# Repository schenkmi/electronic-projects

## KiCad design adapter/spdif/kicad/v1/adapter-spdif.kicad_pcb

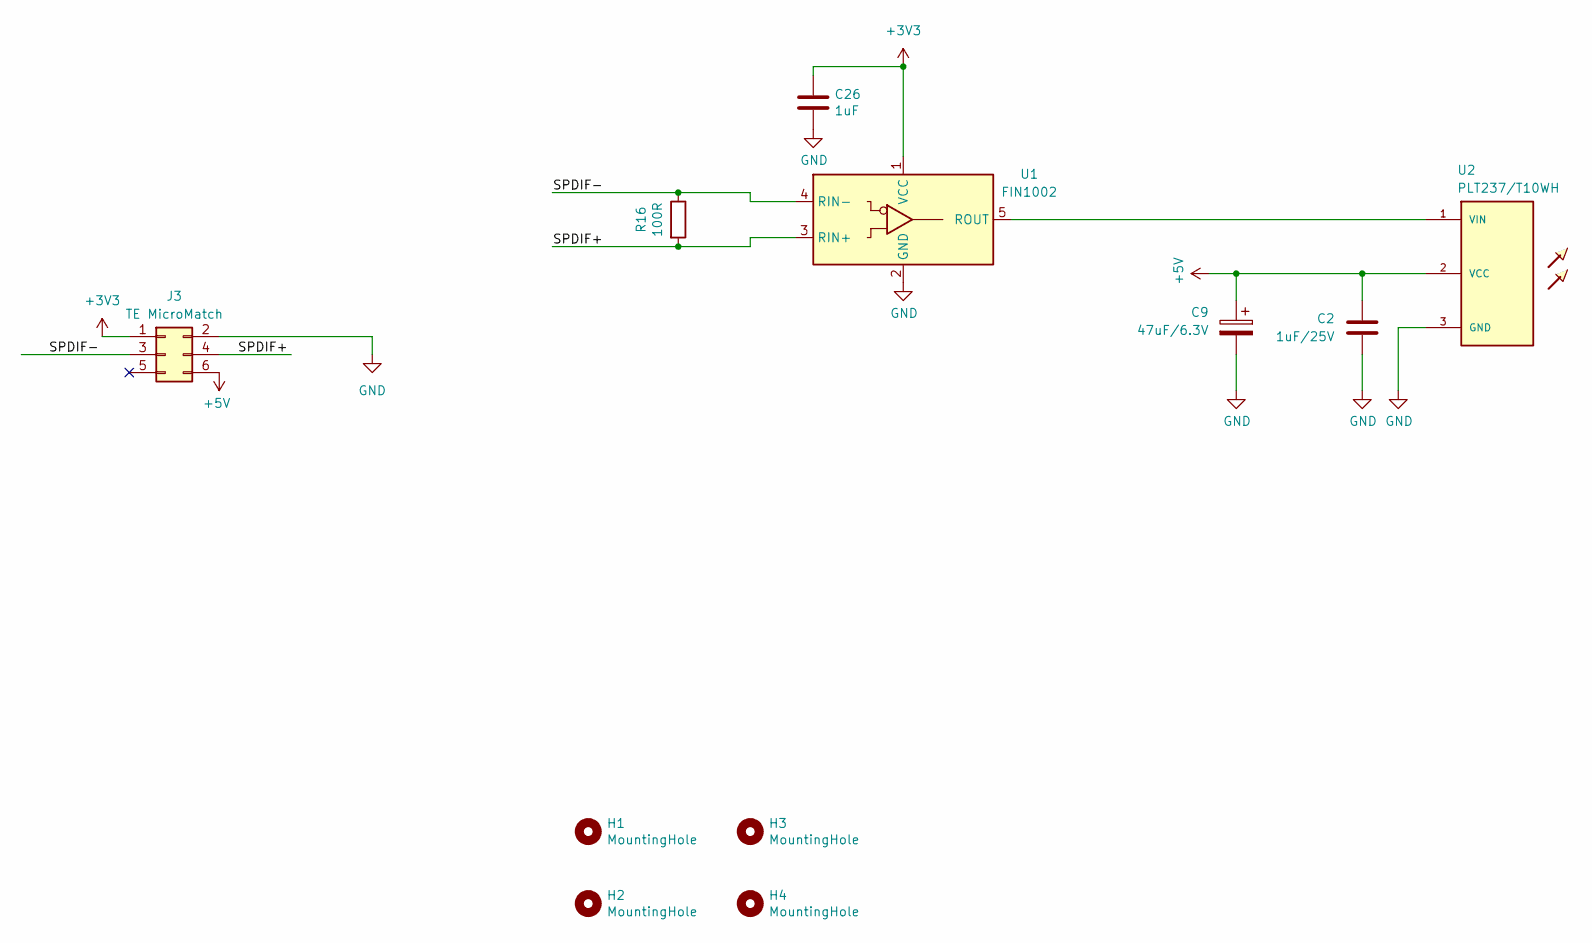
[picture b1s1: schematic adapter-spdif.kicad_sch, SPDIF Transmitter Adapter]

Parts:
C2: 1uF/25V; C_0603_1608Metric_Pad1.08x0.95mm_HandSolder
C9: 47uF/6.3V; C_1206_3216Metric_Pad1.33x1.80mm_HandSolder
C26: 1uF; C_0805_2012Metric_Pad1.18x1.45mm_HandSolder
H1, H2, H3, H4: MountingHole; MountingHole_3.2mm_M3_Pad_Via
J3: TE MicroMatch; TE_Micro-MaTch_215079-6_2x03_P1.27mm_Vertical
R16: 100R; R_0805_2012Metric_Pad1.20x1.40mm_HandSolder
U1: FIN1002; SOT-23-5_HandSoldering; Part Number FIN1002M5X
U2: PLT237/T10WH; PLR135-T10_PLT133-T10W

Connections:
+3V3: C26.1, J3.1, U1.1 (VCC)
+5V: C2.1, C9.1, J3.6, U2.2 (VCC)
/SPDIF+: J3.4, R16.2, U1.3 (RIN+)
/SPDIF-: J3.3, R16.1, U1.4 (RIN-)
GND: C2.2, C9.2, C26.2, J3.2, U1.2 (GND), U2.3 (GND)
unnamed: U1.5 (ROUT), U2.1 (VIN)

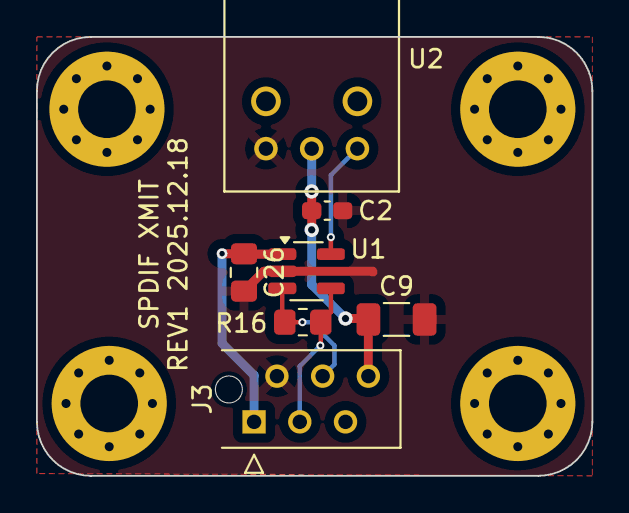
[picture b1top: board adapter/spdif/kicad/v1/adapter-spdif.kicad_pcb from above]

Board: 2 copper layers, 30.9 x 24.4 mm, 11 parts (0 on the bottom side), 6 nets.

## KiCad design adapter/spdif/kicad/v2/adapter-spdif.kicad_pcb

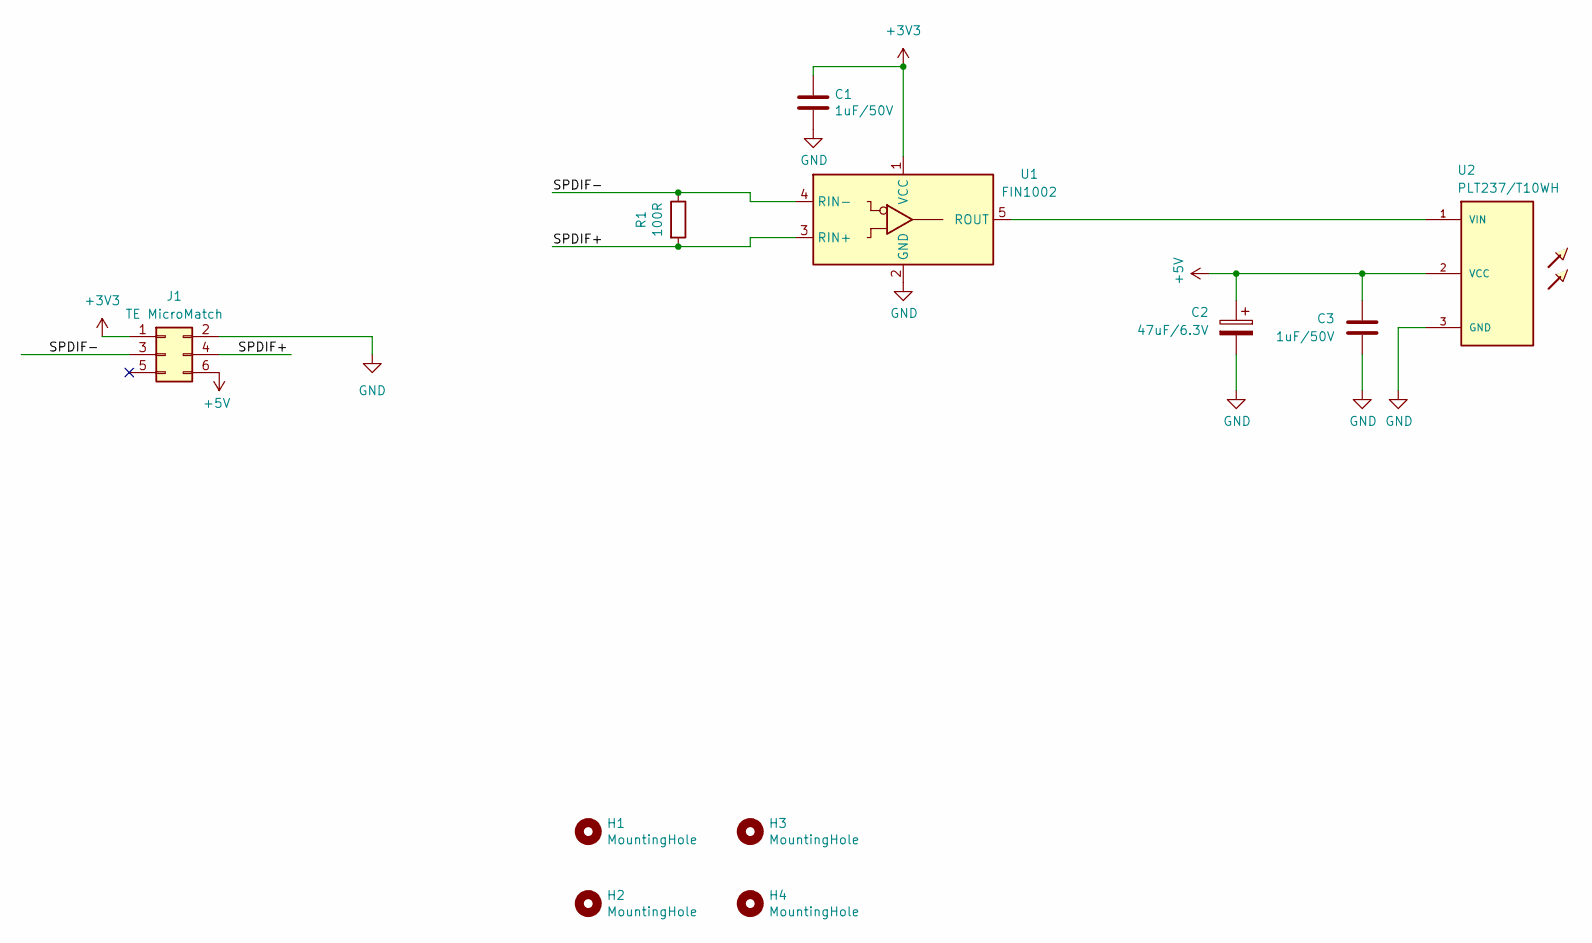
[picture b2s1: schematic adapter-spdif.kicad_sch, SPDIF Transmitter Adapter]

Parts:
C1, C3: 1uF/50V; C_0805_2012Metric_Pad1.18x1.45mm_HandSolder
C2: 47uF/6.3V; C_1206_3216Metric_Pad1.33x1.80mm_HandSolder
H1, H2, H3, H4: MountingHole; MountingHole_3.2mm_M3_Pad_Via
J1: TE MicroMatch; TE_Micro-MaTch_215079-6_2x03_P1.27mm_Vertical
R1: 100R; R_0805_2012Metric_Pad1.20x1.40mm_HandSolder
U1: FIN1002; SOT-23-5_HandSoldering; Part Number FIN1002M5X
U2: PLT237/T10WH; PLR135-T10_PLT133-T10W

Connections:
+3V3: C1.1, J1.1, U1.1 (VCC)
+5V: C2.1, C3.1, J1.6, U2.2 (VCC)
/SPDIF+: J1.4, R1.2, U1.3 (RIN+)
/SPDIF-: J1.3, R1.1, U1.4 (RIN-)
GND: C1.2, C2.2, C3.2, J1.2, U1.2 (GND), U2.3 (GND)
unnamed: U1.5 (ROUT), U2.1 (VIN)

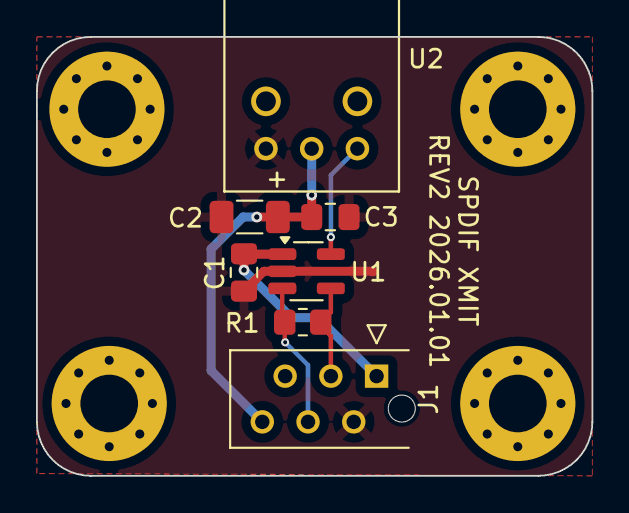
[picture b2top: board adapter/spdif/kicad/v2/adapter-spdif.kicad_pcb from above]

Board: 2 copper layers, 30.9 x 24.4 mm, 11 parts (0 on the bottom side), 6 nets.

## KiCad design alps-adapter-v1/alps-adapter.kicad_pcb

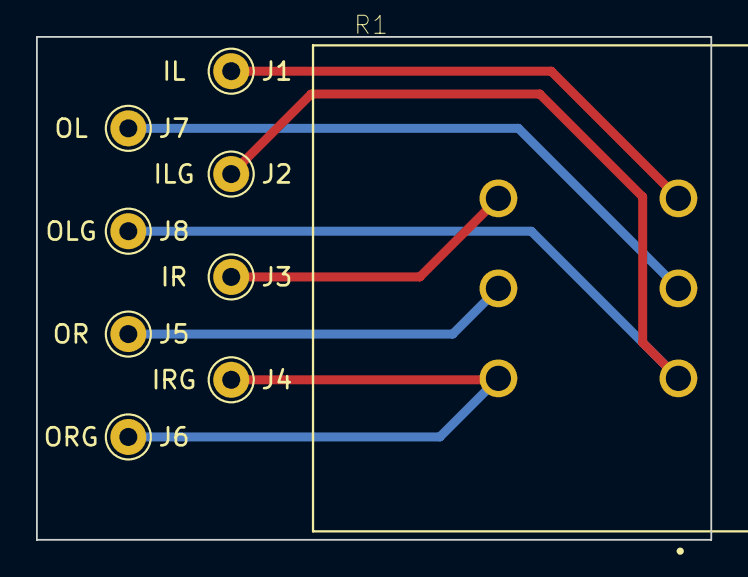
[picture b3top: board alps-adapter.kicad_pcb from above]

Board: 2 copper layers, 37.5 x 27.9 mm, 9 parts (0 on the bottom side), 6 nets.

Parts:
J1: INL; Pin_D1.0mm_L10.0mm
J2: INL_GND; Pin_D1.0mm_L10.0mm
J3: INR; Pin_D1.0mm_L10.0mm
J4: INR_GND; Pin_D1.0mm_L10.0mm
J5: OUTR; Pin_D1.0mm_L10.0mm
J6, J8: OUTR_GND; Pin_D1.0mm_L10.0mm
J7: OUTL; Pin_D1.0mm_L10.0mm
R1: RK27112A0S20C0A103; TRIM_RK27112A0S20C0A103

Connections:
unnamed: J1.1, R1.3_1
unnamed: J2.1, J8.1, R1.1_1
unnamed: J3.1, R1.3_2
unnamed: J4.1, J6.1, R1.1_2
unnamed: J5.1, R1.2_2
unnamed: J7.1, R1.2_1

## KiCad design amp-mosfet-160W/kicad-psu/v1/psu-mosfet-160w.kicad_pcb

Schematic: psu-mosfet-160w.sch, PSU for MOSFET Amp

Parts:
C1: 2.2nF 2kV; C_Rect_L18.0mm_W5.0mm_P15.00mm_FKS3_FKP3
C2, C3: Cx/10nF/100V; C_0805_2012Metric_Pad1.18x1.45mm_HandSolder
C4, C5: Cs/100V; C_1206_3216Metric_Pad1.33x1.80mm_HandSolder
C6, C7, C8, C9: 10000uF/100V; CP_Radial_D40.0mm_P10.00mm_SnapIn
C10, C11: 100n; C_Rect_L7.2mm_W2.5mm_P5.00mm_FKS2_FKP2_MKS2_MKP2
D1, D2, D3, D4: BYV98-200; SOD64-10
J1, J3: Screw_Terminal_01x03; TerminalBlock_RND_205-00013_1x03_P5.00mm_Horizontal
J2: EARTH; Pin_D1.3mm_L11.0mm
MK1, MK2, MK3, MK4: Mounting_Hole_PAD; MountingHole_3.2mm_M3
R1: 100R/2W; R_Axial_DIN0414_L11.9mm_D4.5mm_P15.24mm_Horizontal
R2, R3: Rs/1/8W; R_0805_2012Metric_Pad1.20x1.40mm_HandSolder

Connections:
GND: C1.2, C2.2, C3.1, C5.1, C6.2, C7.1, C8.2, C9.1, C10.2, C11.1, J1.2, J3.2, R1.2, R2.2
unnamed: C1.1, J2.1, R1.1
unnamed: C2.1, C4.1, D1.1 (K), D3.2 (A), J1.1
unnamed: C3.2, D2.1 (K), D4.2 (A), J1.3, R3.2
unnamed: C4.2, R2.1
unnamed: C5.2, R3.1
unnamed: C6.1, C8.1, C10.1, D3.1 (K), D4.1 (K), J3.1
unnamed: C7.2, C9.2, C11.2, D1.2 (A), D2.2 (A), J3.3

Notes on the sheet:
Snubber
Cs=100nF/50 Rs=25.8R/0.125W

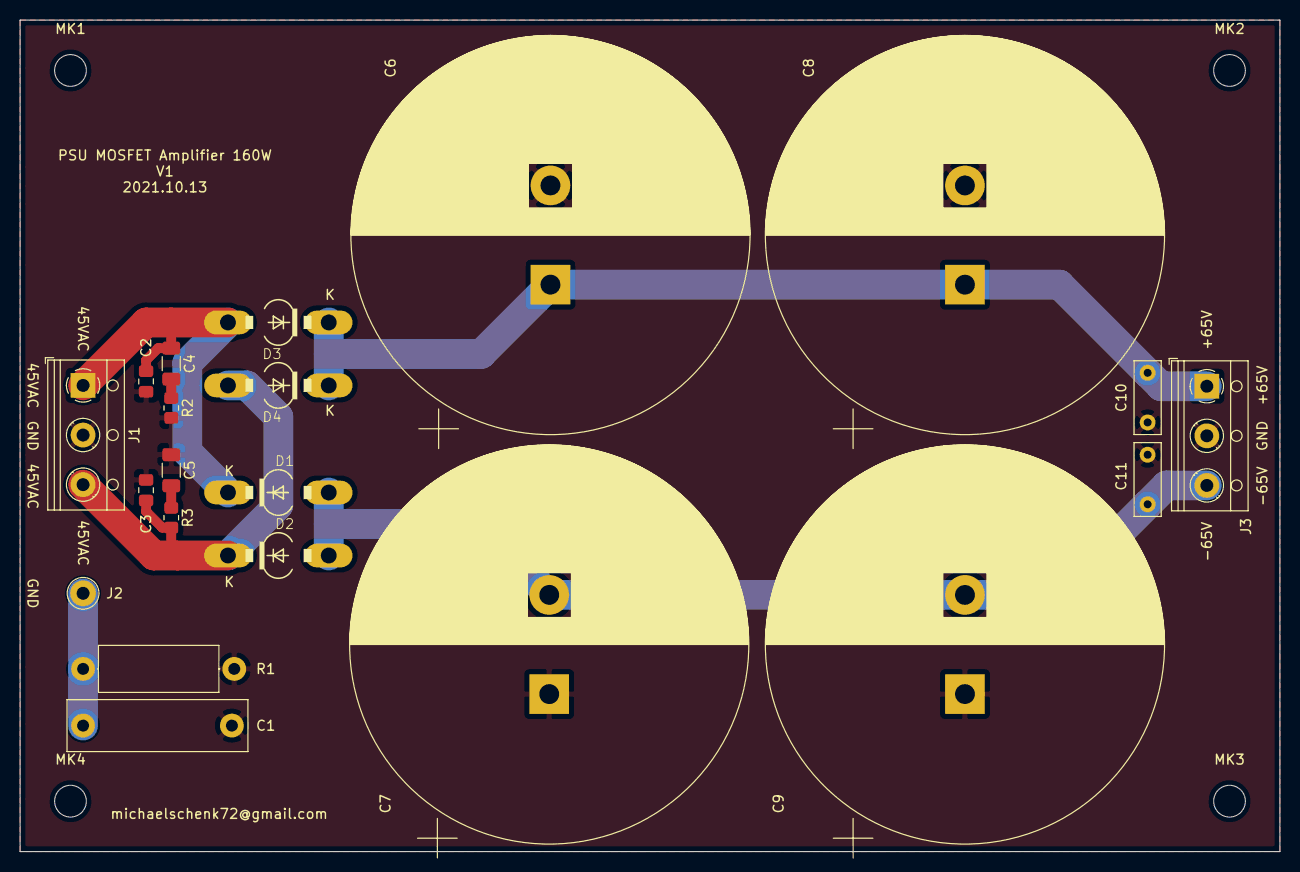
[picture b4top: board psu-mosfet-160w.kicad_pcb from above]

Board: 2 copper layers, 127.0 x 83.8 mm, 25 parts (0 on the bottom side), 8 nets.

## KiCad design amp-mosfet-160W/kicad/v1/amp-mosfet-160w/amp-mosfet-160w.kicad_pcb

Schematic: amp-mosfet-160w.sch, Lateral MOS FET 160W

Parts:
C1: 2.2uF; C_Rect_L7.2mm_W7.2mm_P5.00mm_FKS2_FKP2_MKS2_MKP2
C2: 1n; C_Rect_L7.2mm_W2.5mm_P5.00mm_FKS2_FKP2_MKS2_MKP2
C3: 10n; C_Rect_L7.2mm_W2.5mm_P5.00mm_FKS2_FKP2_MKS2_MKP2
C4: 47u/16V; CP_Radial_D5.0mm_P2.00mm
C5: 10p; C_Rect_L7.2mm_W2.5mm_P5.00mm_FKS2_FKP2_MKS2_MKP2
C6, C7, C9, C10, C14, C18: 100n; C_Rect_L7.2mm_W2.5mm_P5.00mm_FKS2_FKP2_MKS2_MKP2
C8: 18p; C_Rect_L7.2mm_W2.5mm_P5.00mm_FKS2_FKP2_MKS2_MKP2
C11, C12: 100u/100V; CP_Radial_D10.0mm_P5.00mm
C13: 22n; C_Rect_L7.2mm_W2.5mm_P5.00mm_FKS2_FKP2_MKS2_MKP2
C15: 330p; C_Rect_L7.2mm_W2.5mm_P5.00mm_FKS2_FKP2_MKS2_MKP2
C16: 220n; C_Rect_L7.2mm_W2.5mm_P5.00mm_FKS2_FKP2_MKS2_MKP2
C17: 470p; C_Rect_L7.2mm_W2.5mm_P5.00mm_FKS2_FKP2_MKS2_MKP2
D1, D3: 1N914; D_DO-35_SOD27_P7.62mm_Horizontal
D2, D4: 12V/0.5W; D_DO-35_SOD27_P10.16mm_Horizontal
D5, D6: 1N4002; D_DO-41_SOD81_P10.16mm_Horizontal
J1, J2: Conn_01x01; Pin_D1.3mm_L11.0mm
J3: +69V; SolderWire-1.5sqmm_1x01_D1.7mm_OD3.9mm
J4: -69V; SolderWire-1.5sqmm_1x01_D1.7mm_OD3.9mm
J5: LS+; SolderWire-1.5sqmm_1x01_D1.7mm_OD3.9mm
J6: LS-; SolderWire-1.5sqmm_1x01_D1.7mm_OD3.9mm
J7: GND; SolderWire-1.5sqmm_1x01_D1.7mm_OD3.9mm
JP1, JP2: Jump; PinHeader_1x02_P2.54mm_Vertical
MK1, MK2, MK3, MK4: Mounting_Hole_PAD; MountingHole_3.2mm_M3_Pad_Via
Q1, Q6, Q7, Q8: BC556; TO-92_Inline
Q2, Q10: MJE340; TO-126-3_Horizontal_TabDown
Q3, Q9: MJE350; TO-126-3_Horizontal_TabDown
Q4, Q11: ECX10P20; TO-247-3_Horizontal_TabDown
Q5, Q12: ECX10N20; TO-247-3_Horizontal_TabDown
R1, R11: 33k; R_Axial_DIN0207_L6.3mm_D2.5mm_P10.16mm_Horizontal
R2, R10: 1k; R_Axial_DIN0207_L6.3mm_D2.5mm_P10.16mm_Horizontal
R3, R6: 22k; R_Axial_DIN0207_L6.3mm_D2.5mm_P10.16mm_Horizontal
R4, R7: 4k7; R_Axial_DIN0207_L6.3mm_D2.5mm_P10.16mm_Horizontal
R5: 680R; R_Axial_DIN0207_L6.3mm_D2.5mm_P10.16mm_Horizontal
R8, R12, R17, R18, R20: 100R; R_Axial_DIN0207_L6.3mm_D2.5mm_P10.16mm_Horizontal
R9: 12k/1W; R_Axial_DIN0414_L11.9mm_D4.5mm_P15.24mm_Horizontal
R13, R14, R21, R22: 220R; R_Axial_DIN0207_L6.3mm_D2.5mm_P10.16mm_Horizontal
R15, R16, R23, R24: 0.22R; R_Axial_DIN0918_L18.0mm_D9.0mm_P25.40mm_Horizontal
R19: 6.8R/1W; R_Axial_DIN0414_L11.9mm_D4.5mm_P15.24mm_Horizontal
RV1: 200R; Potentiometer_Bourns_3296W_Vertical

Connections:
GND: C2.2, C4.2, C6.2, C9.2, C10.1, C11.2, C12.1, C14.2, C18.1, J2.1, J6.1, J7.1, R1.2, R3.2, R19.2
unnamed: C1.1, R1.1, R2.2
unnamed: C1.2, J1.1
unnamed: C2.1, Q1.2 (B), R2.1
unnamed: C3.1, Q3.2 (C), Q3.3 (B), Q9.3 (B), R9.1
unnamed: C3.2, Q2.2 (C), R9.2
unnamed: C4.1, C6.1, R10.2
unnamed: C5.2, Q8.2 (B), R10.1, R11.2
unnamed: C7.1, C8.2, D4.2 (A), Q10.2 (C), R13.2, R14.2, RV1.2, RV1.3
unnamed: C7.2, D1.2 (A), Q9.2 (C), R21.2, R22.2, RV1.1
unnamed: C8.1, Q1.1 (C), Q10.3 (B), R4.1
unnamed: C10.2, C12.2, R4.2, R7.2, R12.2, R18.2
unnamed: C9.1, C11.1, Q6.3 (E), R5.1, R8.1, R17.1, R20.1
unnamed: C5.1, C13.1, D2.2 (A), D3.2 (A), J5.1, R11.1, R15.1, R16.1, R23.2, R24.2
unnamed: C13.2, R19.1
unnamed: C14.1, J3.1, JP1.2, Q5.3 (D), Q12.3 (D)
unnamed: C15.1, C16.2, Q5.2 (S), R23.1
unnamed: C15.2, Q5.1 (G), R22.1
unnamed: C16.1, C17.1, Q12.2 (S), R24.1
unnamed: C17.2, Q12.1 (G), R21.1
unnamed: C18.2, J4.1, JP2.1, Q4.3 (S), Q11.3 (S)
unnamed: D1.1 (K), D2.1 (K)
unnamed: D3.1 (K), D4.1 (K)
unnamed: D5.1 (K), R17.2
unnamed: D5.2 (A), JP1.1
unnamed: D6.1 (K), JP2.2
unnamed: D6.2 (A), R18.1
unnamed: Q1.3 (E), Q8.3 (E), R6.2
unnamed: Q2.3 (B), Q8.1 (C), R7.1
unnamed: Q3.1 (E), R8.2
unnamed: Q4.1 (G), R13.1
unnamed: Q4.2 (D), R15.2
unnamed: Q6.1 (C), Q7.2 (B), R3.1
unnamed: Q6.2 (B), Q7.3 (E), R5.2
unnamed: Q7.1 (C), R6.1
unnamed: Q9.1 (E), R20.2
unnamed: Q2.1 (E), Q10.1 (E), R12.1
unnamed: Q11.1 (G), R14.1
unnamed: Q11.2 (D), R16.2

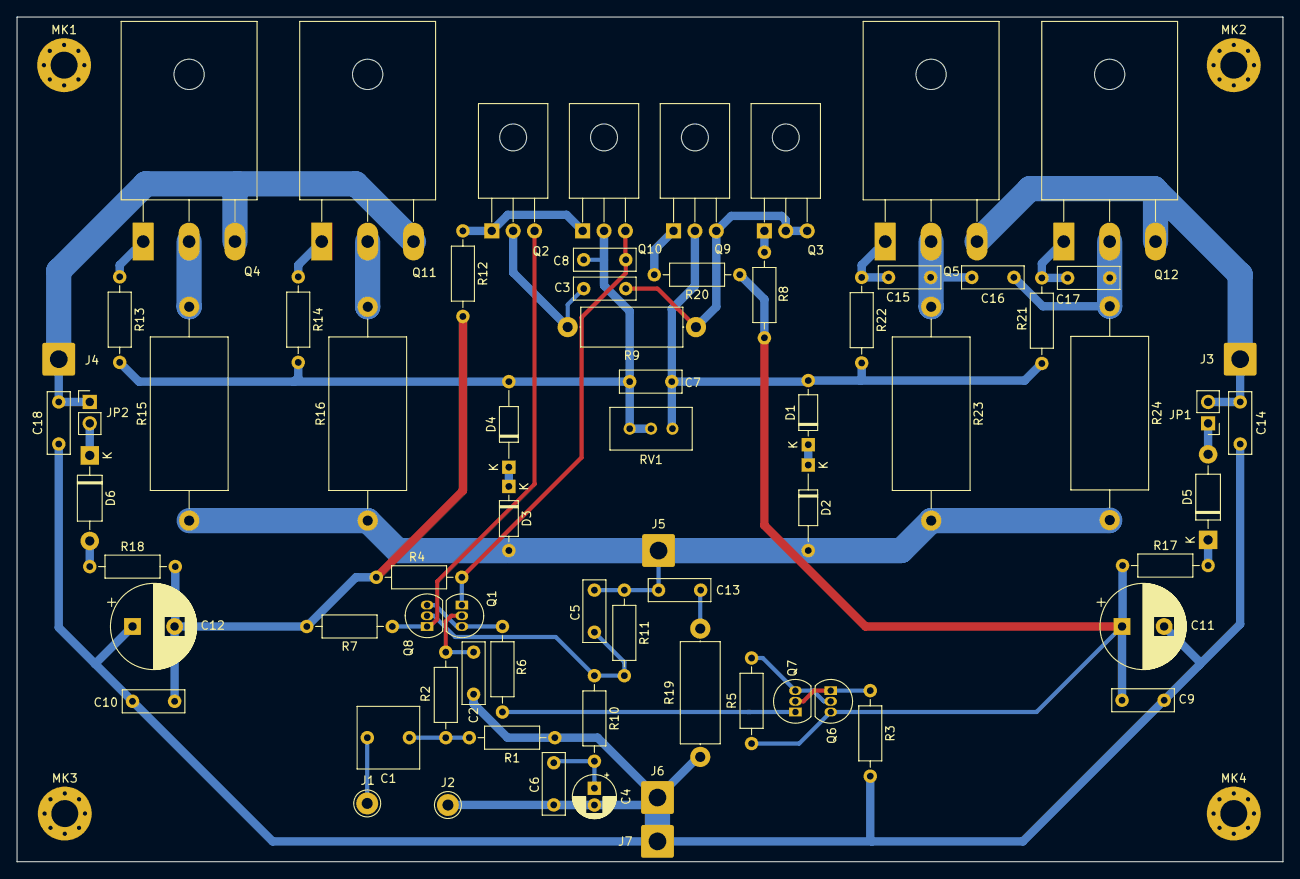
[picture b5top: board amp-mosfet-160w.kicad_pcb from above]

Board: 2 copper layers, 150.4 x 100.3 mm, 74 parts (0 on the bottom side), 39 nets.
